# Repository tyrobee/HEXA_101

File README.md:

# HEXA_101
A esp 32 based hexapod

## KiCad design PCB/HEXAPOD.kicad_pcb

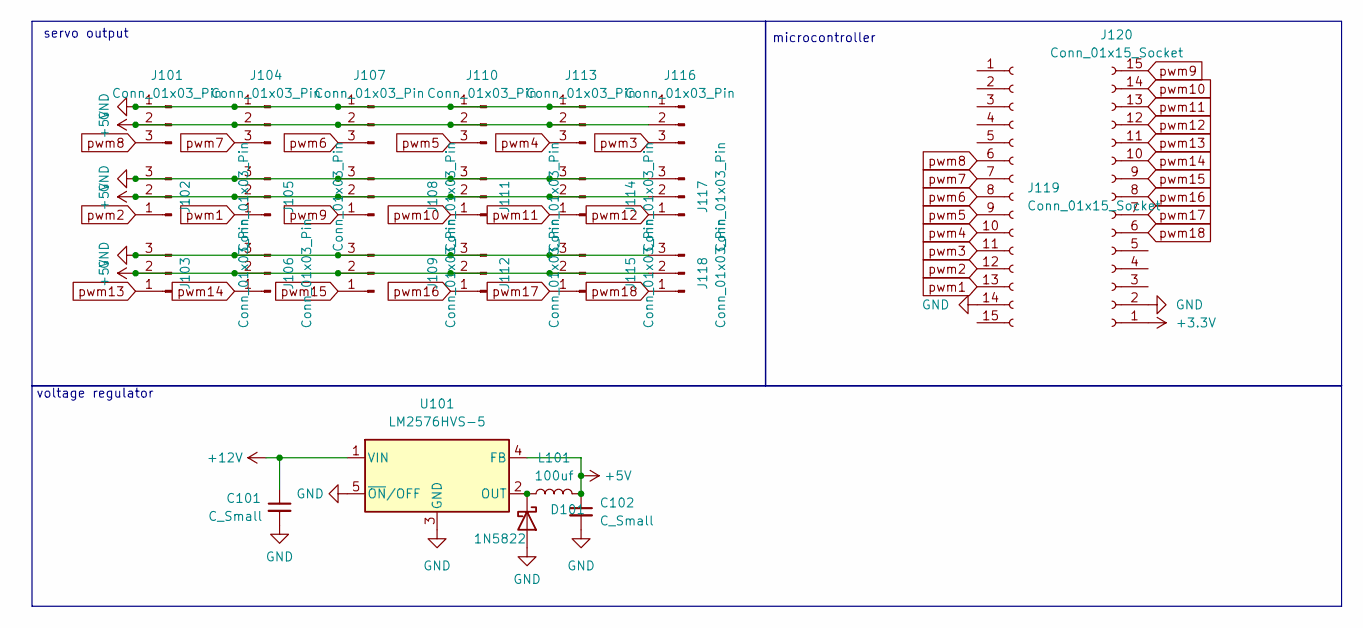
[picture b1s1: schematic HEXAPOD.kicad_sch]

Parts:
C101, C102: C_Small; C_Radial_D6.3mm_H11.0mm_P2.50mm
D101: 1N5822; D_DO-201AD_P15.24mm_Horizontal
J101, J102, J103, J104, J105, J106, J107, J108, J109, J110, J111, J112, J113, J114, J115, J116, J117, J118: Conn_01x03_Pin; PinHeader_1x03_P2.54mm_Vertical
J119, J120: Conn_01x15_Socket; PinSocket_1x15_P2.54mm_Vertical
L101: 100uf; L_Radial_D10.0mm_P5.00mm_Fastron_07M
U101: LM2576HVS-5; TO-263-5_TabPin3

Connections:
+3.3V: J120.1
+5V: C102.1, J101.2, J102.2, J103.2, J104.2, J105.2, J106.2, J107.2, J108.2, J109.2, J110.2, J111.2, J112.2, J113.2, J114.2, J115.2, J116.2, J117.2, J118.2, L101.2, U101.4 (FB)
+12V: C101.1, U101.1 (VIN)
GND: C101.2, C102.2, D101.2 (A), J101.1, J102.3, J103.3, J104.1, J105.3, J106.3, J107.1, J108.3, J109.3, J110.1, J111.3, J112.3, J113.1, J114.3, J115.3, J116.1, J117.3, J118.3, J119.14, J120.2, U101.3 (GND), U101.5 (~ON/OFF)
unnamed: D101.1 (K), L101.1, U101.2 (OUT)
pwm1: J105.1, J119.13
pwm2: J102.1, J119.12
pwm3: J116.3, J119.11
pwm4: J113.3, J119.10
pwm5: J110.3, J119.9
pwm6: J107.3, J119.8
pwm7: J104.3, J119.7
pwm8: J101.3, J119.6
pwm9: J108.1, J120.15
pwm10: J111.1, J120.14
pwm11: J114.1, J120.13
pwm12: J117.1, J120.12
pwm13: J103.1, J120.11
pwm14: J106.1, J120.10
pwm15: J109.1, J120.9
pwm16: J112.1, J120.8
pwm17: J115.1, J120.7
pwm18: J118.1, J120.6

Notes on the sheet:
voltage regulator
microcontroller
servo output

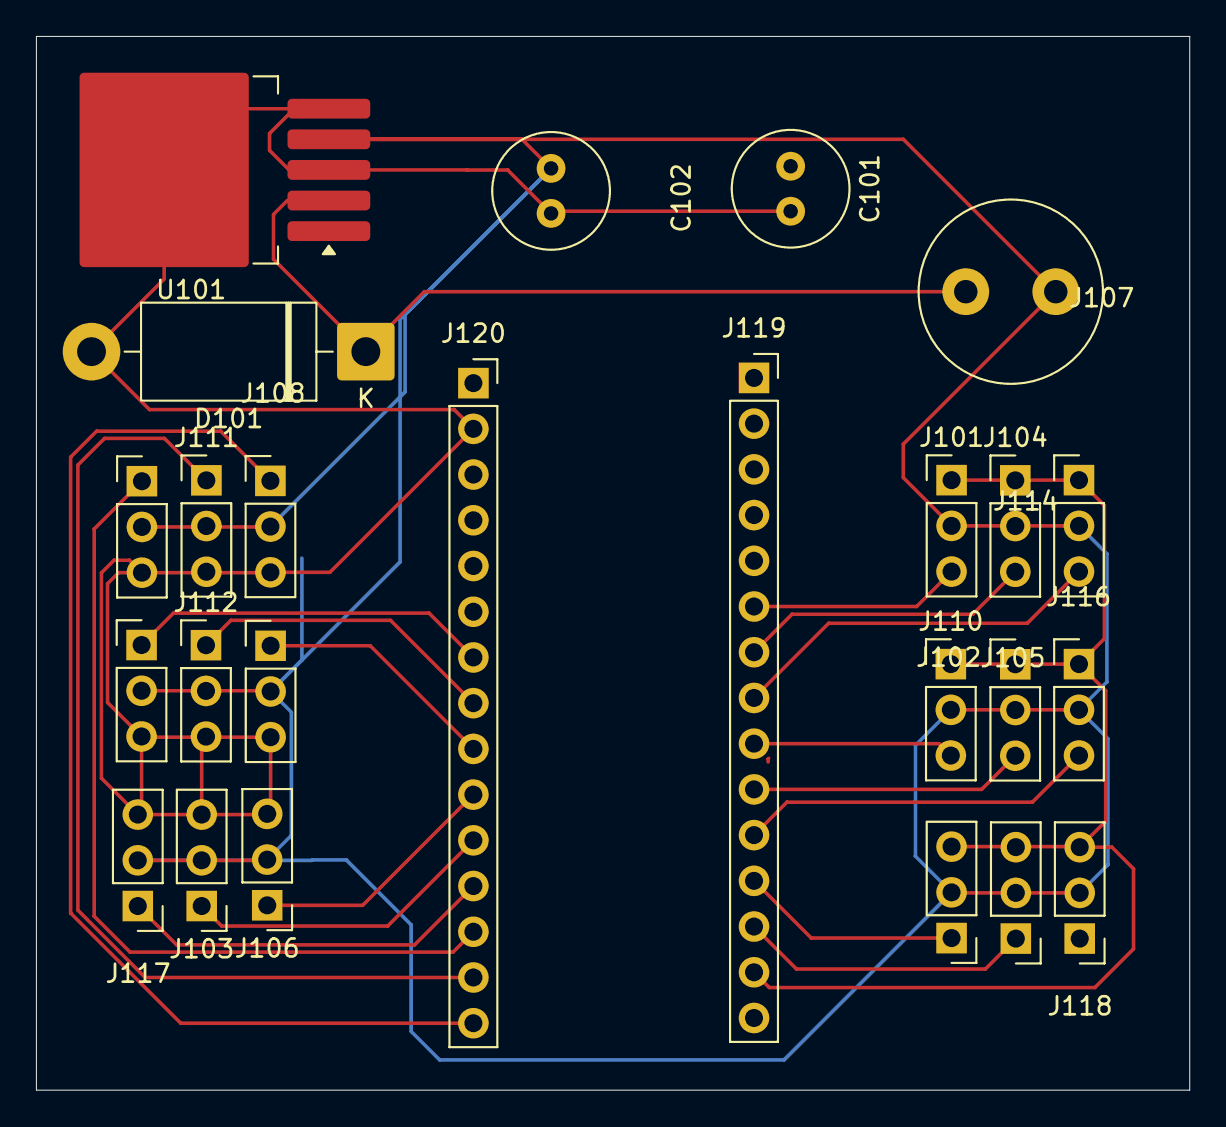
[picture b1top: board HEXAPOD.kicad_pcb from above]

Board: 2 copper layers, 64.1 x 58.5 mm, 25 parts (0 on the bottom side), 22 nets.

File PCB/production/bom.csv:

Designator,Footprint,Quantity,Value,LCSC Part #
"C101, C102",C_Radial_D6.3mm_H11.0mm_P2.50mm,2,C_Small,
D101,D_DO-201AD_P15.24mm_Horizontal,1,1N5822,
"J101, J102, J103, J104, J105, J106, J107, J108, J109, J110, J111, J112, J113, J114, J115, J116, J117, J118",PinHeader_1x03_P2.54mm_Vertical,18,Conn_01x03_Pin,
"J119, J120",PinSocket_1x15_P2.54mm_Vertical,2,Conn_01x15_Socket,
L101,L_Radial_D10.0mm_P5.00mm_Fastron_07M,1,100uf,
U101,TO-263-5_TabPin3,1,LM2576HVS-5,
